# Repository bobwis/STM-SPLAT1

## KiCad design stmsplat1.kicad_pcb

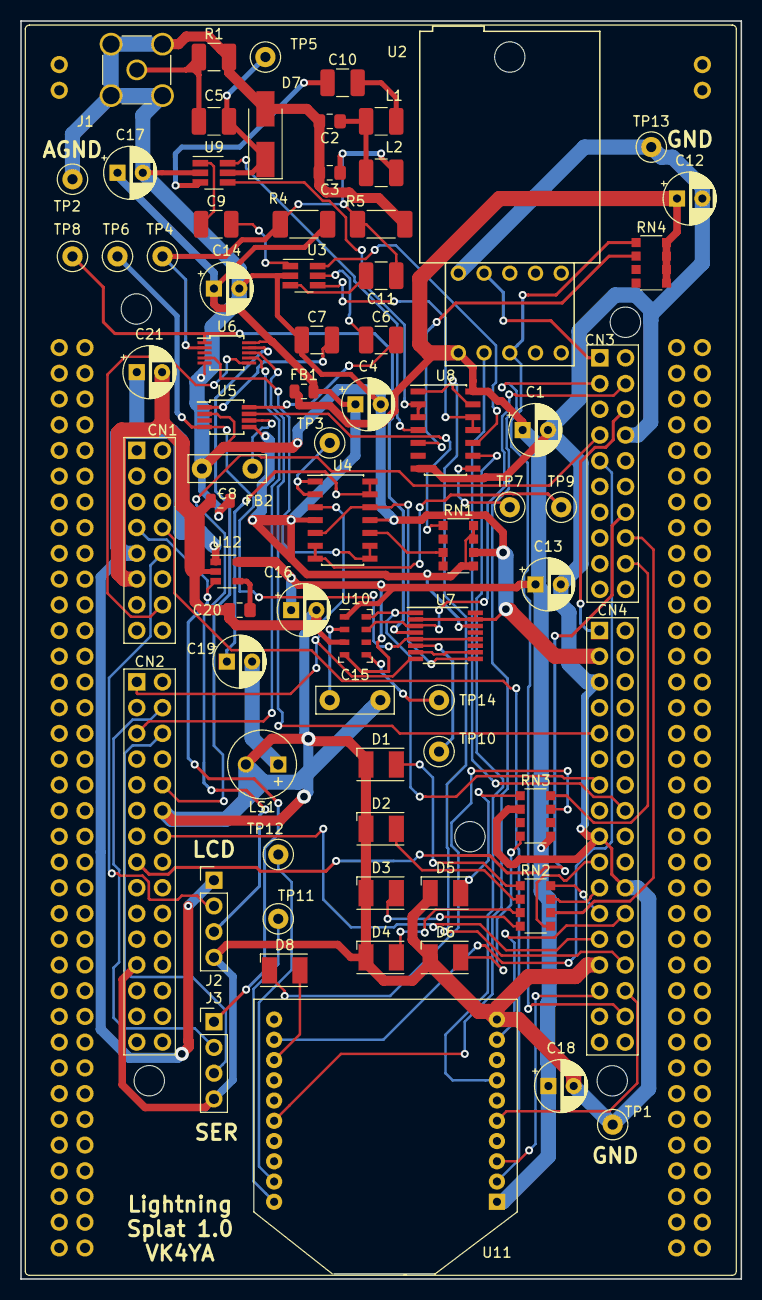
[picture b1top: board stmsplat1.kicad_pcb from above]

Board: 2 copper layers, 71.1 x 124.2 mm, 74 parts (0 on the bottom side), 80 nets.

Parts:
C1, C12, C14, C19: 1uF; CP_Radial_D5.0mm_P2.50mm
C2: 560pF; C_0805_2012Metric_Pad1.15x1.40mm_HandSolder
C3: 240pF; C_0805_2012Metric_Pad1.15x1.40mm_HandSolder
C4, C13, C18: 10uF; CP_Radial_D5.0mm_P2.50mm
C5, C6, C7, C9, C10, C11: 47n; C_1210_3225Metric_Pad1.42x2.65mm_HandSolder
C8: 25pF; C_Disc_D7.5mm_W2.5mm_P5.00mm
C15: 100nF; C_Disc_D7.5mm_W2.5mm_P5.00mm
C16, C17, C21: 100uF; CP_Radial_D5.0mm_P2.50mm
C20: 470pF; C_0805_2012Metric_Pad1.15x1.40mm_HandSolder
CN1: Conn_01x16_Male; IDC-Pins_2x8_P2.54mm_Vertical
CN2: Conn_01x30_Male; IDC-Pins_2x15_P2.54mm_Vertical
CN3: Conn_01x20_Male; IDC-Pins_2x10_P2.54mm_Vertical
CN4: Conn_01x34_Male; IDC-Pins_2x17_P2.54mm_Vertical
D1, D2, D3, D4, D5, D6, D8: LED; LED_PLCC-2
D7: SMAJ8.0CA Bourns 9V; D_SMA_Handsoldering
FB1, FB2: Ferrite_Bead; L_0805_2012Metric
J1: Conn_Coaxial; SMA_Amphenol_132134-11_Vertical
J2, J3: Conn_01x04_Male; PinHeader_1x04_P2.54mm_Vertical
L1: 620nH; L_1210_3225Metric_Pad1.42x2.65mm_HandSolder
L2: 1.5uH; L_1210_3225Metric_Pad1.42x2.65mm_HandSolder
LS1: Speaker; MagneticBuzzer_Kingstate_KCG0601
R1: 53R; C_1210_3225Metric_Pad1.42x2.65mm_HandSolder
R4, R5: 100R; R_2010_5025Metric_Pad1.52x2.65mm_HandSolder
RN1, RN4: 4K7; R_Array_Convex_4x1206
RN2, RN3: 470R; R_Array_Convex_4x1206
TP1, TP2, TP3, TP4, TP5, TP6, TP7, TP8, TP9, TP10, TP11, TP12, TP13, TP14: TestPoint; TestPoint_Loop_D1.80mm_Drill1.0mm_Beaded
U1: NUCLEO144-F746ZG; ST_Nucleo_144_Large_Daughter
U2: ublox_chinese_PCB_module; GPS_IDC-Header_2x05_P2.54mm_Horizontal
U3, U9: HMC544A-RF_Switch; SOT-23-6_Handsoldering
U4: Opamp_Quad_MCP6024; SOIC-14_3.9x8.7mm_P1.27mm
U5: AD8310; MSOP-8_3x3mm_P0.65mm
U6: MCP6S93-X_UN; MSOP-10_3x3mm_P0.5mm
U7: ADG729; TSSOP-16_4.4x5mm_P0.65mm
U8: 74HC04; SOIC-14_3.9x8.7mm_P1.27mm
U10: MPL315A2; LGA-8_3x5mm_P1.25mm
U11: XBee3; XBEE-22MM-TH
U12: MIC5219-3.3YM5; SOT-23-5

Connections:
/+3V3: CN1.7, J3.1, U12.3
/+5V: C21.1, CN1.9, J2.1, U12.1
/A3V3: C4.1, C14.1, C17.1, FB1.2, R4.1, RN1.5, RN1.7, RN1.8, U4.4, U5.5, U6.10, U7.14
/AMPOUT: TP8.1, U6.1, U7.4
/AVDD: CN3.6, CN4.1
/DAC1: U7.7, U7.10
/HALF3V3: U4.8, U4.9, U6.4
/LOGOUT: TP6.1, U5.4, U7.5, U7.12
/P3V3: C1.1, C12.1, C13.1, C16.1, C18.1, FB1.1, RN3.5, RN4.5, RN4.6, RN4.7, RN4.8, U2.1, U8.14, U10.1, U10.4, U11.1, U12.5
/PA0: CN4.29, U11.3
/PA3: CN2.1, U4.3, U7.8
/PA7: CN2.15, CN3.14
/PA15: CN3.9, U11.12
/PB6: CN4.13, U7.1, U10.8
/PB9: CN3.4, U7.3, U10.7
/PB10: CN4.32, RN4.1, U2.5
/PB12: CN3.7, J2.3
/PB15: CN3.3, U11.16
/PC2: CN4.9, U6.8
/PC3: CN2.5, U6.7
/PC6: CN3.1, U2.4
/PC11: CN1.8, U11.2
/PC12: CN1.10, J2.2
/PD3: CN2.10, U6.9
/PD5: CN2.6, J3.3
/PD6: CN2.4, J3.2
/PD11: CN4.23, RN2.8
/PD12: CN4.21, RN2.7
/PD13: CN4.19, RN2.5
/PD14: CN3.16, RN2.6
/PD15: CN3.18, RN3.8
/PE2: CN2.14, CN4.25
/PE10: CN4.24, U11.9
/PE14: CN4.28, U8.1, U8.13
/PE15: CN4.30, U11.5
/PG2: CN1.14, U6.6
/PG9: CN4.16, U2.3
/XB_PIO4: D8.1, RN3.7
AGND: C2.2, C3.2, C4.2, C7.1, C8.2, C14.2, C17.2, CN4.3, D7.2, FB2.1, J1.2, R1.2, R5.2, RN1.6, TP2.1, U3.2, U4.11, U5.2, U6.5, U7.2, U7.15, U7.16, U9.2
GND: C1.2, C12.2, C13.2, C15.2, C16.2, C18.2, C20.2, C21.2, CN1.11, CN2.12, CN2.23, CN3.8, CN4.5, CN4.17, CN4.22, CN4.27, D1.1, D2.1, D3.1, D4.1, D5.1, D6.1, FB2.2, J2.4, J3.4, LS1.2, RN3.2, TP1.1, TP13.1, U2.2, U8.7, U10.3, U11.10, U12.2
unnamed: C2.1, L1.1, L2.2
unnamed: C5.1, D7.1, TP5.1, U9.5
unnamed: C5.2, J1.1, R1.1
unnamed: C6.1, U3.5
unnamed: C6.2, U5.8
unnamed: C7.2, U5.1
unnamed: C8.1, U5.6
unnamed: C9.1, U9.1
unnamed: C9.2, U3.1
unnamed: C10.1, U9.3
unnamed: C10.2, L1.2
unnamed: C3.1, C11.1, L2.1, R4.2, R5.1, TP4.1, U6.2
unnamed: C11.2, U3.3
unnamed: C15.1, U10.2
unnamed: C19.1, U4.13, U4.14
unnamed: C19.2, LS1.1
unnamed: C20.1, U12.4
unnamed: D1.2, RN2.1
unnamed: D2.2, RN2.2
unnamed: D3.2, RN2.4
unnamed: D4.2, RN2.3
unnamed: D5.2, RN3.1
unnamed: D6.2, RN3.4
unnamed: D8.2, U11.13
unnamed: RN1.1, U5.7
unnamed: RN1.3, RN1.4, U4.10
unnamed: RN4.2, U8.5
unnamed: TP3.1, U4.1, U4.2
unnamed: TP7.1, U8.8
unnamed: TP9.1, U4.6, U4.7
unnamed: TP10.1, U7.6
unnamed: TP11.1, U11.20
unnamed: TP12.1, U11.19
unnamed: TP14.1, U10.5
unnamed: U3.4, U8.11, U8.12
unnamed: U3.6, U8.10
unnamed: U4.5, U4.12, U7.9
unnamed: U8.2, U8.3, U9.4
unnamed: U8.4, U9.6
unnamed: U8.9, U11.7

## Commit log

2018-10-25 Worked on PCB outline and connectors
    Initial Commit
2018-10-26 Experimented with KiCad operations
    Tried new symbols / footprints etc
2018-10-27 minor changes - still experimenting
2018-10-29 pcb outline and start trim of connectors
2018-10-30 Getting ready for proper start to project
2018-10-30 Arduino connectors moved to correct position
2018-10-31 Cropped PCB to clear STM board buttons
    Added GPS module connector and silkscreen
2018-10-31 Footprints re-assigned
    PCB had lost associations
2018-10-31 Added Arduino Header Labels
2018-11-09 Added input lowpass filter
2018-11-17 Added more
2018-11-17 Zigbee added
    Trial placement 1
2018-11-18 XBee changes, more STM interconnect detail
2018-11-20 Initial design captured
2018-11-21 Chenged input and filter matching arrangement
2018-11-21 Add snapshot of schematic
    For review outside of kicad
2018-11-25 Bugger about
2018-11-25 Revert "Bugger about"
    This reverts commit de86f82cdc59ddff2c2c92d76c25a3b15eaa12e2.
2018-11-25 Stuff done by paul
2018-11-25 Add GPS and Debug Serial Comms connections
2018-12-20 placement improvements
2018-12-20 silkscreen mods, small placement changes
2018-12-22 2nd go at manual routing. Via sizes may all be small.
2018-12-23 Fix Xbee extra symbol pin, change via sizes on power
2018-12-23 Update schematic
2018-12-23 Before splitting drive to RF switches
2018-12-23 Split drive to RF switches
2019-01-05 Prepared for PCB production
    Several PCB tracking changes and footprint tweaks etc
2019-01-05 Silkcreen Tidy
2019-01-05 Sent to PCB maker
